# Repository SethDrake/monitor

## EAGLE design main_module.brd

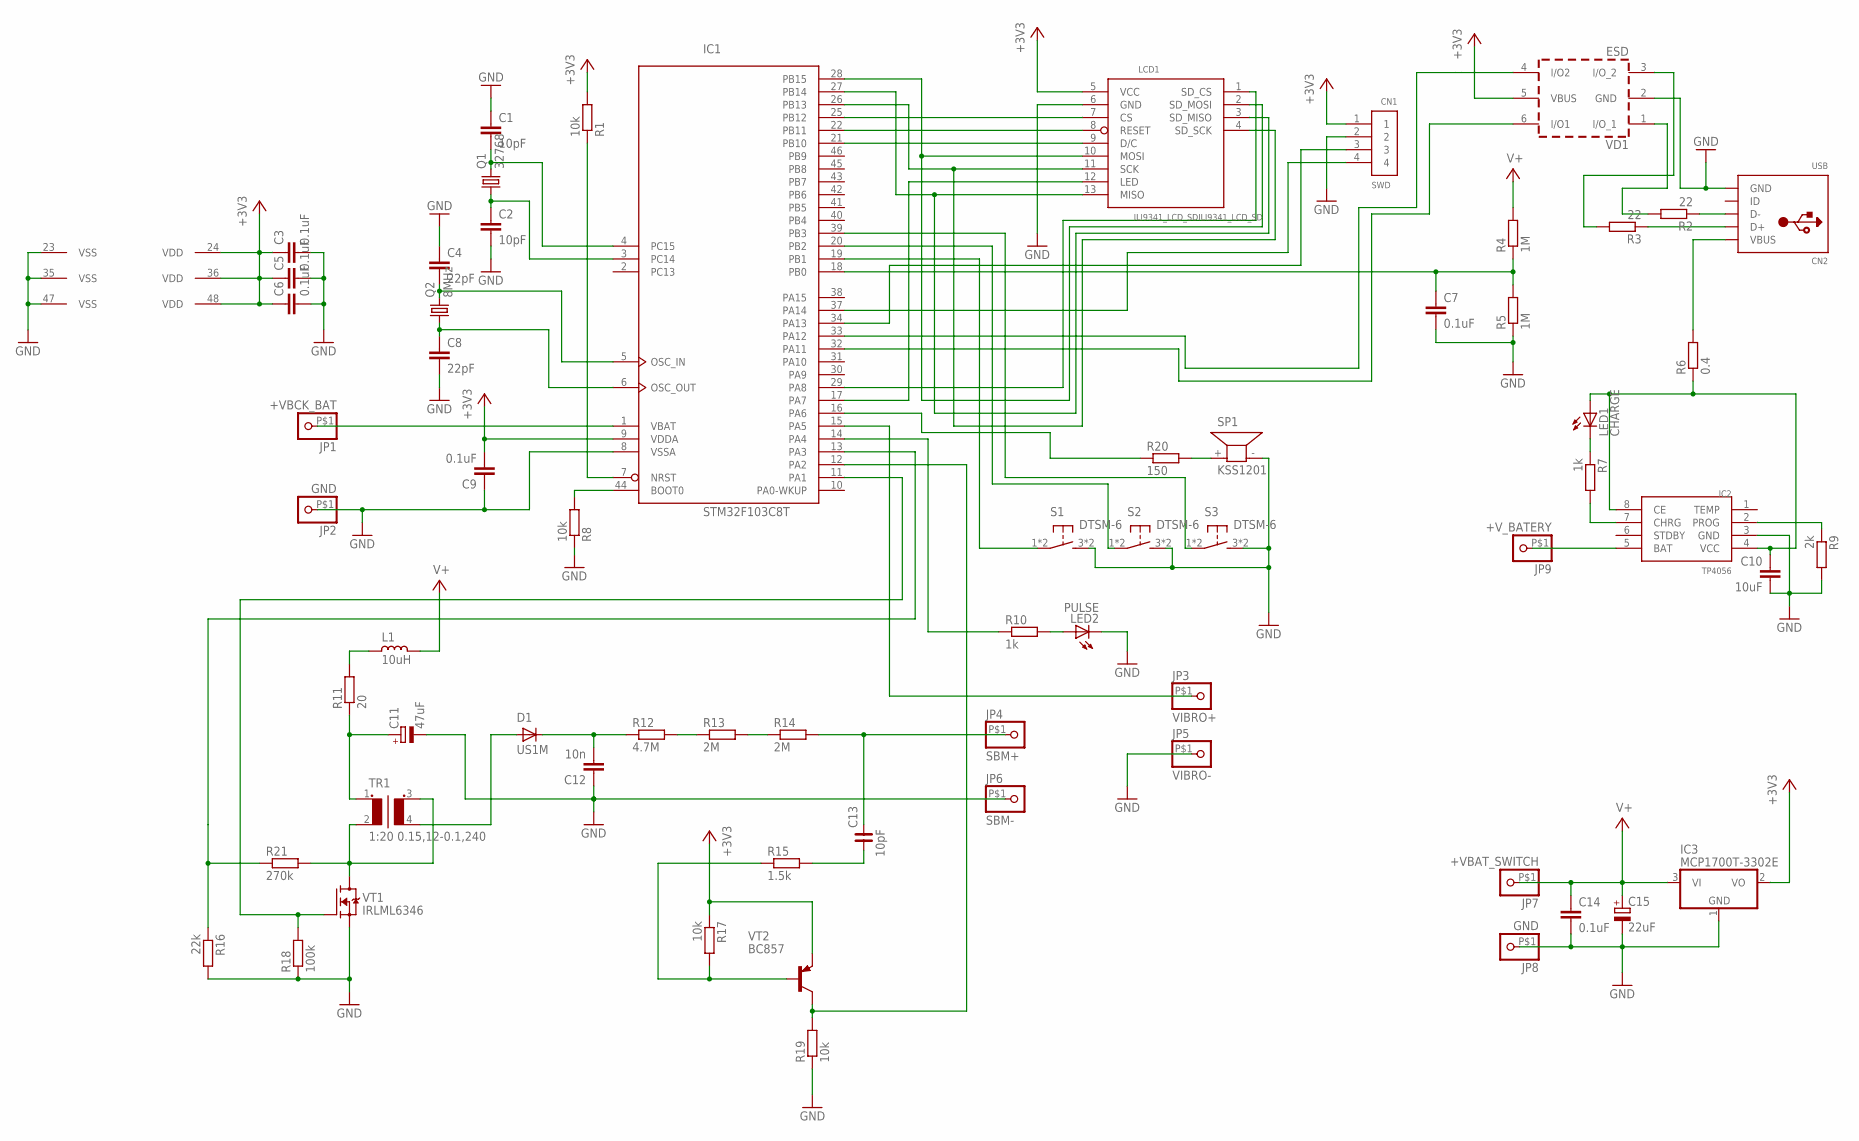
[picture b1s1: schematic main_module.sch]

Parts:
C1, C2: 10pF; C0805
C3, C5, C6, C7, C9, C14: 0.1uF; C0805
C4, C8: 22pF; C0805
C10: 10uF; C0805
C11: 47uF; C/6032-28R
C12: 10n; C1206
C13: 10pF; C1206
C15: 22uF; C/6032-28R
CN1: SWD; 1X04-BIG
CN2: USB; USB-MINIB
D1: US1M; SMA-DO214AC
IC1: STM32F103C8T; LQFP48
IC2: TP4056; SOP-8
IC3: MCP1700T-3302E; SOT23
JP1: +VBCK_BAT; 1X1-BIGPOGO
JP2, JP8: GND; 1X1-BIGPOGO
JP3: VIBRO+; 1X1-BIGPOGO
JP4: SBM+; 1X1-BIGPOGO
JP5: VIBRO-; 1X1-BIGPOGO
JP6: SBM-; 1X1-BIGPOGO
JP7: +VBAT_SWITCH; 1X1-BIGPOGO
JP9: +V_BATERY; 1X1-BIGPOGO
L1: 10uH; L0805
LCD1: ILI9341_LCD_SDILI9341_LCD_SD; ILI9341_LCD_SD
LED1: CHARGE; CHIP-LED0805
LED2: PULSE; LED3MM
Q1: 32768; HC49/S
Q2: 8MHz; HC49/S
R1, R8, R17, R19: 10k; M0805
R2, R3: 22; M0805
R4, R5: 1M; M0805
R6: 0.4; M1206
R7, R10: 1k; M0805
R9: 2k; M0805
R11: 20; M0805
R12: 4.7M; M0805
R13, R14: 2M; M0805
R15: 1.5k; M0805
R16: 22k; M0805
R18: 100k; M0805
R20: 150; M0805
R21: 270k; M0805
S1, S2, S3: DTSM-6
SP1: KSS1201
TR1: 1:20 0.15,12-0.1,240; RING-TRANS
VD1: ESD; SOT-23-6L
VT1: IRLML6346; SOT23
VT2: BC857; SOT23-BCE

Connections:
32OSC_IN: C1.2, IC1.4 (PC15), Q1.2
32OSC_OUT: C2.1, IC1.3 (PC14), Q1.1
+3V3: C3.1, C5.1, C6.1, C9.2, CN1.1, IC1.9 (VDDA), IC1.24 (VDD), IC1.36 (VDD), IC1.48 (VDD), IC3.2 (VO), LCD1.5 (VCC), R1.2, R17.1, VD1.5 (VBUS), VT2.E
+VBCK_BAT: IC1.1 (VBAT), JP1.P$1
+V_BATTERY: IC2.5 (BAT), JP9.P$1
BATT_CTRL: C7.1, IC1.18 (PB0), R4.1, R5.2
GND: C1.1, C2.2, C3.2, C4.1, C5.2, C6.2, C7.2, C8.2, C9.1, C10.2, C11.-, C12.1, C14.2, C15.-, CN1.2, CN2.GND, IC1.8 (VSSA), IC1.23 (VSS), IC1.35 (VSS), IC1.47 (VSS), IC2.3 (GND), IC3.1 (GND), JP2.P$1, JP5.P$1, JP6.P$1, JP8.P$1, LCD1.6 (GND), LED2.K (C), R5.1, R8.1, R9.2, R16.2, R18.1, R19.1, S1.3, S1.4 (3), S2.3, S2.4 (3), S3.3, S3.4 (3), SP1.- (2), VD1.2 (GND), VT1.2 (S)
HV_OUT: C12.2, D1.K (C), R12.1
HV_PULSE: IC1.12 (PA2), R19.2, VT2.C
HV_PUMP: IC1.11 (PA1), R18.2, VT1.1 (G)
HV_TEST: IC1.13 (PA3), R16.1, R21.1
HV_TR_OUT: D1.A, TR1.4 (S2)
KEY1: IC1.19 (PB1), S1.1, S1.2 (1)
KEY2: IC1.20 (PB2), S2.1, S2.2 (1)
KEY3: IC1.39 (PB3), S3.1, S3.2 (1)
LCD_BACKLIGHT: IC1.17 (PA7), LCD1.12 (LED)
LCD_CS: IC1.25 (PB12), LCD1.7 (CS)
LCD_RESET: IC1.22 (PB11), LCD1.8 (RESET)
LCD_RS: IC1.21 (PB10), LCD1.9 (D/C)
LED_PULSE: IC1.14 (PA4), R10.1
MISO: IC1.27 (PB14), LCD1.3 (SD_MISO), LCD1.13 (MISO)
MOSI: IC1.28 (PB15), LCD1.2 (SD_MOSI), LCD1.10 (MOSI)
unnamed: R13.2, R14.1
unnamed: R20.2, SP1.+ (1)
unnamed: R12.2, R13.1
unnamed: IC1.7 (NRST), R1.1
unnamed: L1.2, R11.2
unnamed: C13.1, R15.2
unnamed: C10.1, IC2.4 (VCC), IC2.8 (CE), LED1.A, R6.1
unnamed: LED2.A, R10.2
unnamed: R15.1, R17.2, VT2.B
unnamed: C11.+, R11.1, TR1.1
unnamed: IC1.44 (BOOT0), R8.2
unnamed: CN2.D-, R2.1
unnamed: CN2.D+, R3.1
unnamed: IC2.2 (PROG), R9.1
unnamed: R21.2, TR1.2, TR1.3 (S1), VT1.3 (D)
unnamed: IC2.7 (CHRG), R7.2
unnamed: LED1.C, R7.1
OSC_IN: C4.2, IC1.5 (OSC_IN), Q2.2
OSC_OUT: C8.1, IC1.6 (OSC_OUT), Q2.1
SBM+: C13.2, JP4.P$1, R14.2
SCK: IC1.26 (PB13), LCD1.4 (SD_SCK), LCD1.11 (SCK)
SD_CS: IC1.29 (PA8), LCD1.1 (SD_CS)
SOUND: IC1.16 (PA6), R20.1
SWCLK: CN1.4, IC1.37 (PA14)
SWDIO: CN1.3, IC1.34 (PA13)
USB_DM: IC1.32 (PA11), VD1.6 (I/O1)
USB_DM_PROT: R2.2, VD1.1 (I/O_1)
USB_DP: IC1.33 (PA12), VD1.4 (I/O2)
USB_DP_PROT: R3.2, VD1.3 (I/O_2)
USB_POWER: CN2.VBUS, R6.2
V+: C14.1, C15.+, IC3.3 (VI), JP7.P$1, L1.1, R4.2
VIBRO: IC1.15 (PA5), JP3.P$1

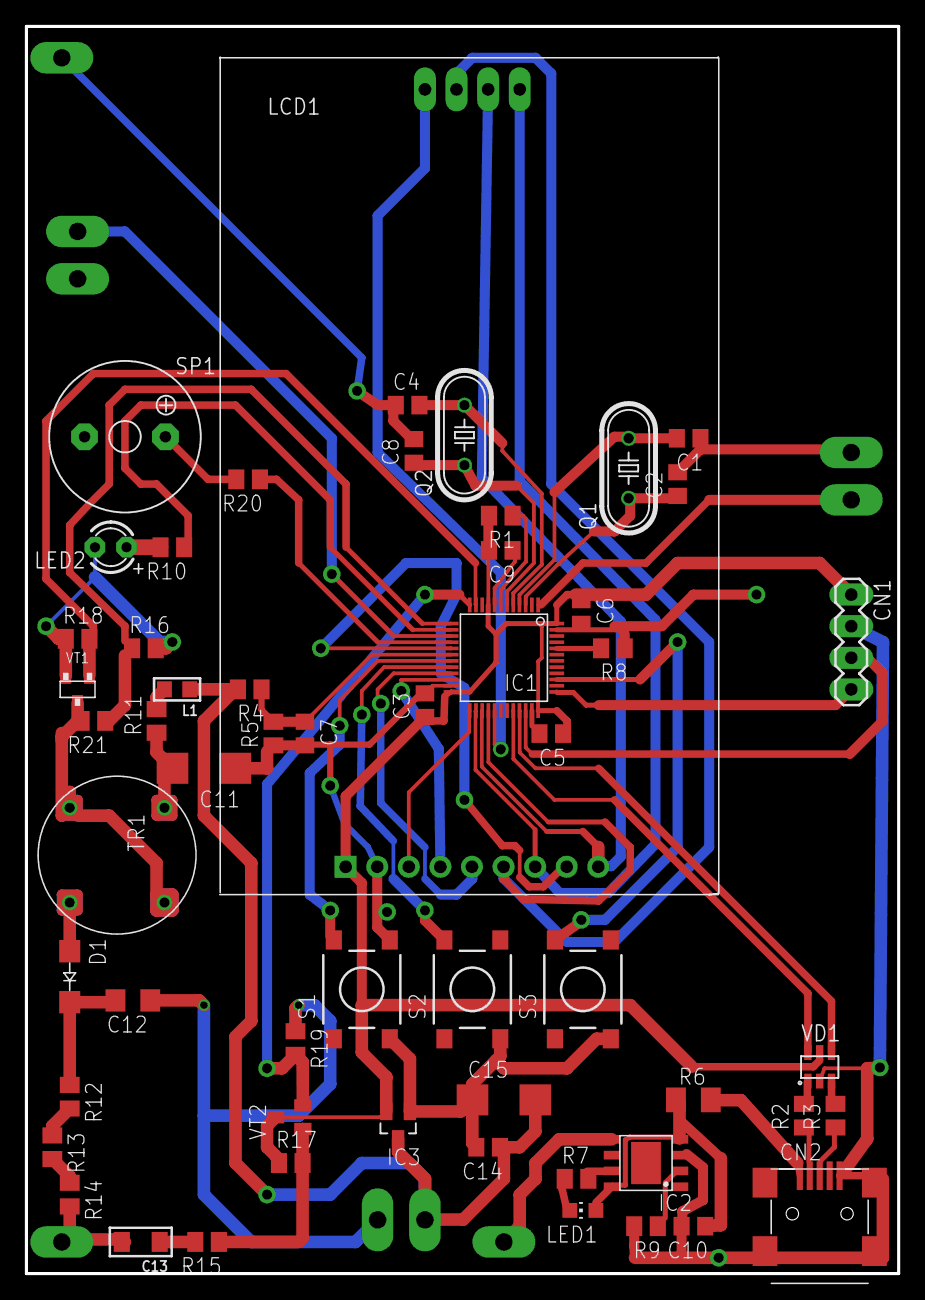
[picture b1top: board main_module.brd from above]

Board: 2 copper layers, 70.2 x 100.3 mm, 65 parts (0 on the bottom side), 54 nets.

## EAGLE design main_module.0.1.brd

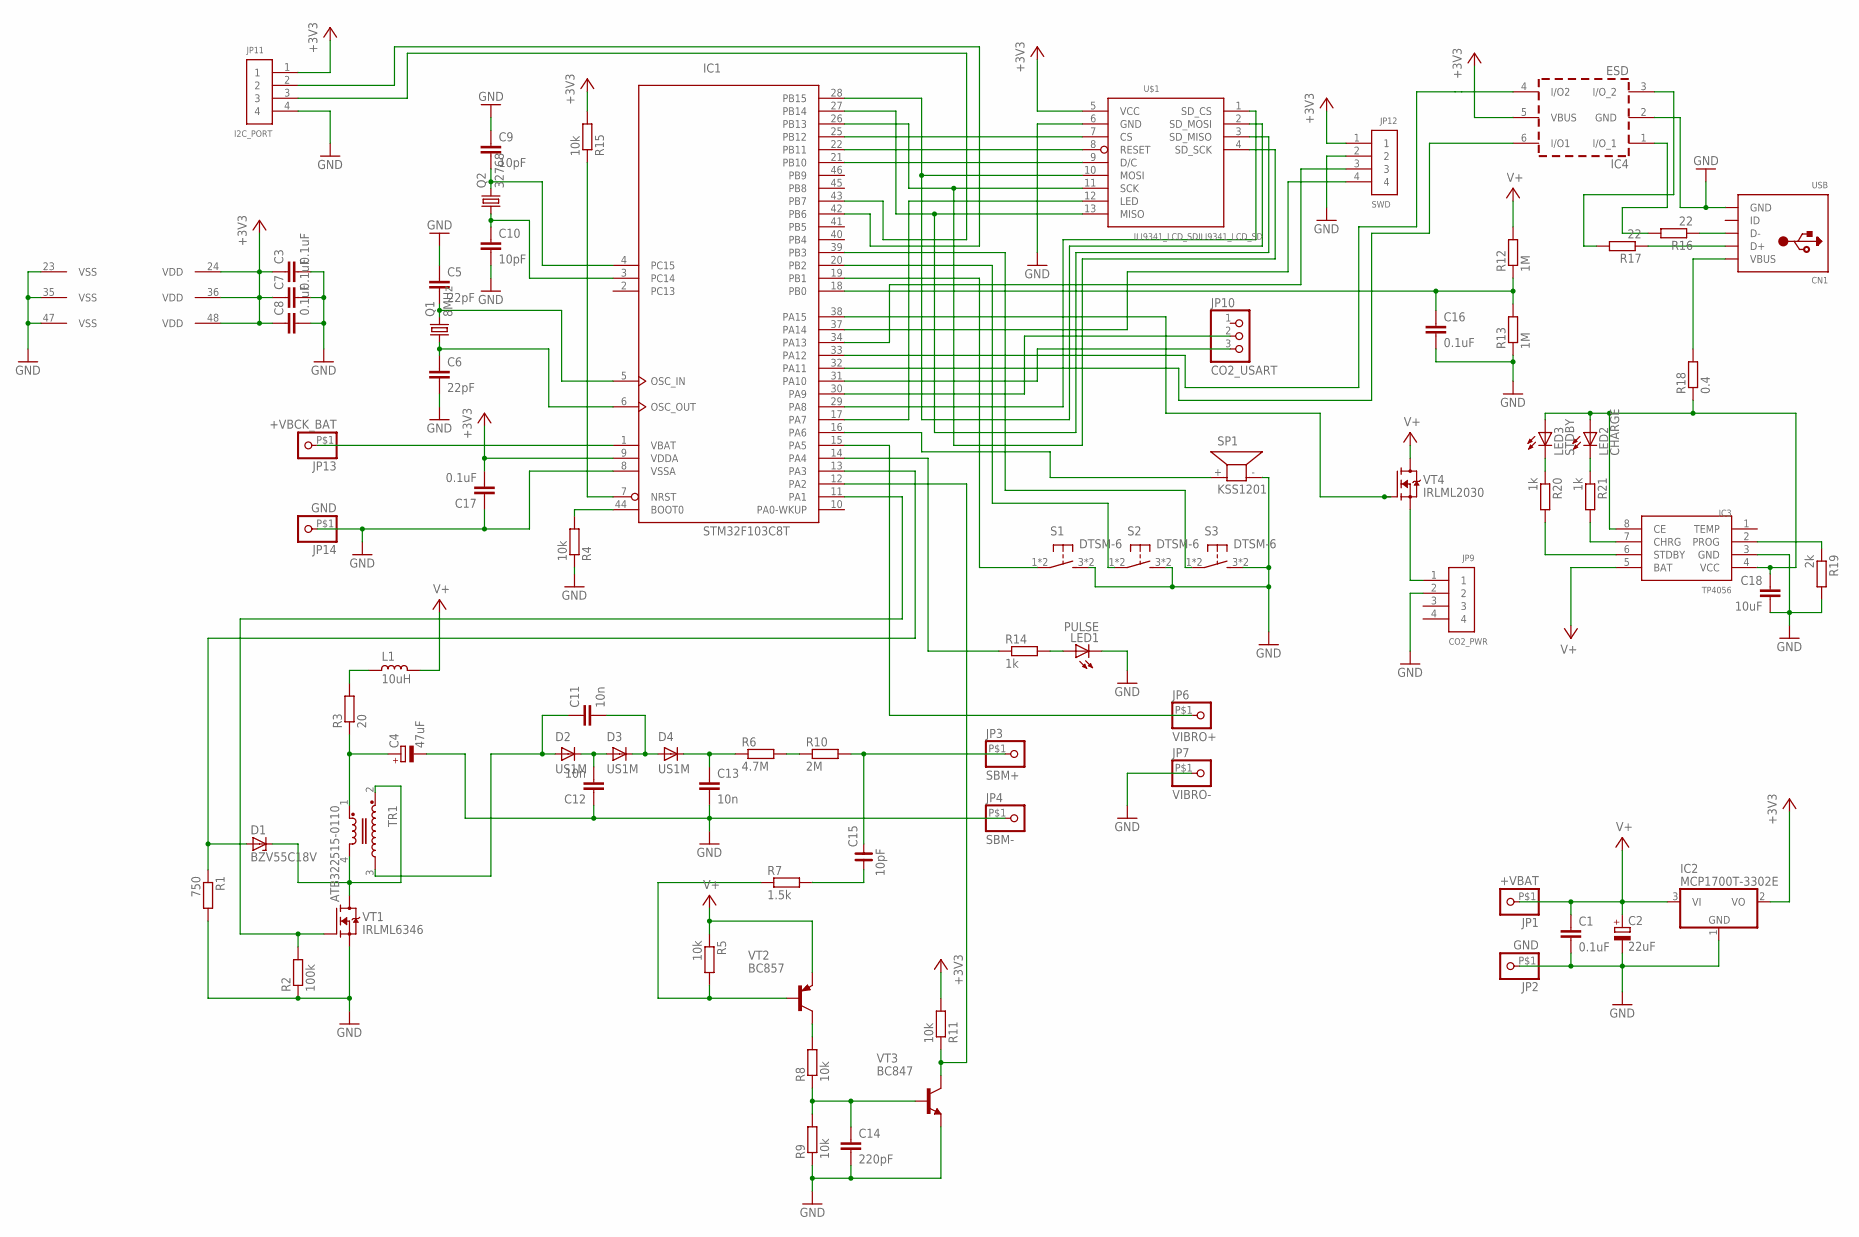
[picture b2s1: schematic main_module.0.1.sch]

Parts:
C1, C3, C7, C8, C16, C17: 0.1uF; C0805
C2: 22uF; C/6032-28R
C4: 47uF; C/6032-28R
C5, C6: 22pF; C0805
C9, C10: 10pF; C0805
C11, C12, C13: 10n; C1206
C14: 220pF; C0805
C15: 10pF; C1206
C18: 10uF; C0805
CN1: USB; USB-MINIB
D1: BZV55C18V; SOD80C
D2, D3, D4: US1M; SMA-DO214AC
IC1: STM32F103C8T; LQFP48
IC2: MCP1700T-3302E; SOT23
IC3: TP4056; SOP-8
IC4: ESD; SOT-23-6L
JP1: +VBAT; 1X1-BIGPOGO
JP2, JP14: GND; 1X1-BIGPOGO
JP3: SBM+; 1X1-BIGPOGO
JP4: SBM-; 1X1-BIGPOGO
JP6: VIBRO+; 1X1-BIGPOGO
JP7: VIBRO-; 1X1-BIGPOGO
JP9: CO2_PWR; 1X04-BIG
JP10: CO2_USART; 1X03
JP11: I2C_PORT; 1X04-BIG
JP12: SWD; 1X04-BIG
JP13: +VBCK_BAT; 1X1-BIGPOGO
L1: 10uH; L0805
LED1: PULSE; LED3MM
LED2: CHARGE; CHIP-LED0805
LED3: STDBY; CHIP-LED0805
Q1: 8MHz; HC49/S
Q2: 32768; HC49/S
R1: 750; M0805
R2: 100k; M0805
R3: 20; M0805
R4, R5, R8, R9, R11, R15: 10k; M0805
R6: 4.7M; M0805
R7: 1.5k; M0805
R10: 2M; M0805
R12, R13: 1M; M0805
R14, R20, R21: 1k; M0805
R16, R17: 22; M0805
R18: 0.4; M1206
R19: 2k; M0805
S1, S2, S3: DTSM-6
SP1: KSS1201
TR1: ATB322515-0110; ATB3225
U$1: ILI9341_LCD_SDILI9341_LCD_SD; ILI9341_LCD_SD
VT1: IRLML6346; SOT23
VT2: BC857; SOT23-BCE
VT3: BC847; SOT23
VT4: IRLML2030; SOT23

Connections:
32OSC_IN: C9.2, IC1.4 (PC15), Q2.2
32OSC_OUT: C10.1, IC1.3 (PC14), Q2.1
+3V3: C3.1, C7.1, C8.1, C17.2, IC1.9 (VDDA), IC1.24 (VDD), IC1.36 (VDD), IC1.48 (VDD), IC2.2 (VO), IC4.5 (VBUS), JP11.1, JP12.1, R11.2, R15.2, U$1.5 (VCC)
+VBCK_BAT: IC1.1 (VBAT), JP13.P$1
BATT_CTRL: C16.1, IC1.18 (PB0), R12.1, R13.2
CO2_PWR_CONTROL: IC1.38 (PA15), VT4.1 (G)
GND: C1.2, C2.-, C3.2, C4.-, C5.1, C6.2, C7.2, C8.2, C9.1, C10.2, C12.1, C13.2, C14.2, C16.2, C17.1, C18.2, CN1.GND, IC1.8 (VSSA), IC1.23 (VSS), IC1.35 (VSS), IC1.47 (VSS), IC2.1 (GND), IC3.3 (GND), IC4.2 (GND), JP2.P$1, JP4.P$1, JP7.P$1, JP9.2, JP11.4, JP12.2, JP14.P$1, LED1.K (C), R1.2, R2.1, R4.1, R9.1, R13.1, R19.2, S1.3, S1.4 (3), S2.3, S2.4 (3), S3.3, S3.4 (3), SP1.- (2), U$1.6 (GND), VT1.2 (S), VT3.2 (E)
HV_MUL_IN: C11.1, D2.A, TR1.3
HV_PULSE: IC1.12 (PA2), R11.1, VT3.3 (C)
HV_PUMP: IC1.11 (PA1), R2.2, VT1.1 (G)
HV_TEST: D1.A, IC1.13 (PA3), R1.1
I2C_SCL: IC1.42 (PB6), JP11.2
I2C_SDA: IC1.43 (PB7), JP11.3
KEY1: IC1.19 (PB1), S1.1, S1.2 (1)
KEY2: IC1.20 (PB2), S2.1, S2.2 (1)
KEY3: IC1.39 (PB3), S3.1, S3.2 (1)
LCD_BACKLIGHT: IC1.17 (PA7), U$1.12 (LED)
LCD_CS: IC1.25 (PB12), U$1.7 (CS)
LCD_RESET: IC1.22 (PB11), U$1.8 (RESET)
LCD_RS: IC1.21 (PB10), U$1.9 (D/C)
LED_PULSE: IC1.14 (PA4), R14.1
MISO: IC1.27 (PB14), U$1.3 (SD_MISO), U$1.13 (MISO)
MOSI: IC1.28 (PB15), U$1.2 (SD_MOSI), U$1.10 (MOSI)
unnamed: JP9.1, VT4.2 (S)
unnamed: C12.2, D2.K (C), D3.A
unnamed: C11.2, D3.K (C), D4.A
unnamed: C13.1, D4.K (C), R6.1
unnamed: R6.2, R10.1
unnamed: IC1.7 (NRST), R15.1
unnamed: L1.2, R3.2
unnamed: C15.1, R7.2
unnamed: C18.1, IC3.4 (VCC), IC3.8 (CE), LED2.A, LED3.A, R18.1
unnamed: LED1.A, R14.2
unnamed: R5.2, R7.1, VT2.B
unnamed: R8.2, VT2.C
unnamed: C14.1, R8.1, R9.2, VT3.1 (B)
unnamed: C4.+, R3.1, TR1.1
unnamed: IC1.44 (BOOT0), R4.2
unnamed: CN1.D-, R16.1
unnamed: CN1.D+, R17.1
unnamed: IC3.2 (PROG), R19.1
unnamed: D1.C, TR1.2, TR1.4, VT1.3 (D)
unnamed: IC3.7 (CHRG), R21.2
unnamed: LED2.C, R21.1
unnamed: LED3.C, R20.1
unnamed: IC3.6 (STDBY), R20.2
OSC_IN: C5.2, IC1.5 (OSC_IN), Q1.2
OSC_OUT: C6.1, IC1.6 (OSC_OUT), Q1.1
SBM+: C15.2, JP3.P$1, R10.2
SCK: IC1.26 (PB13), U$1.4 (SD_SCK), U$1.11 (SCK)
SD_CS: IC1.29 (PA8), U$1.1 (SD_CS)
SOUND: IC1.16 (PA6), SP1.+ (1)
SWCLK: IC1.37 (PA14), JP12.4
SWDIO: IC1.34 (PA13), JP12.3
USART_RX: IC1.31 (PA10), JP10.3
USART_TX: IC1.30 (PA9), JP10.2
USB_DM: IC1.32 (PA11), IC4.6 (I/O1)
USB_DM_PROT: IC4.1 (I/O_1), R16.2
USB_DP: IC1.33 (PA12), IC4.4 (I/O2)
USB_DP_PROT: IC4.3 (I/O_2), R17.2
USB_POWER: CN1.VBUS, R18.2
V+: C1.1, C2.+, IC2.3 (VI), IC3.5 (BAT), JP1.P$1, L1.1, R5.1, R12.2, VT2.E, VT4.3 (D)
VIBRO: IC1.15 (PA5), JP6.P$1

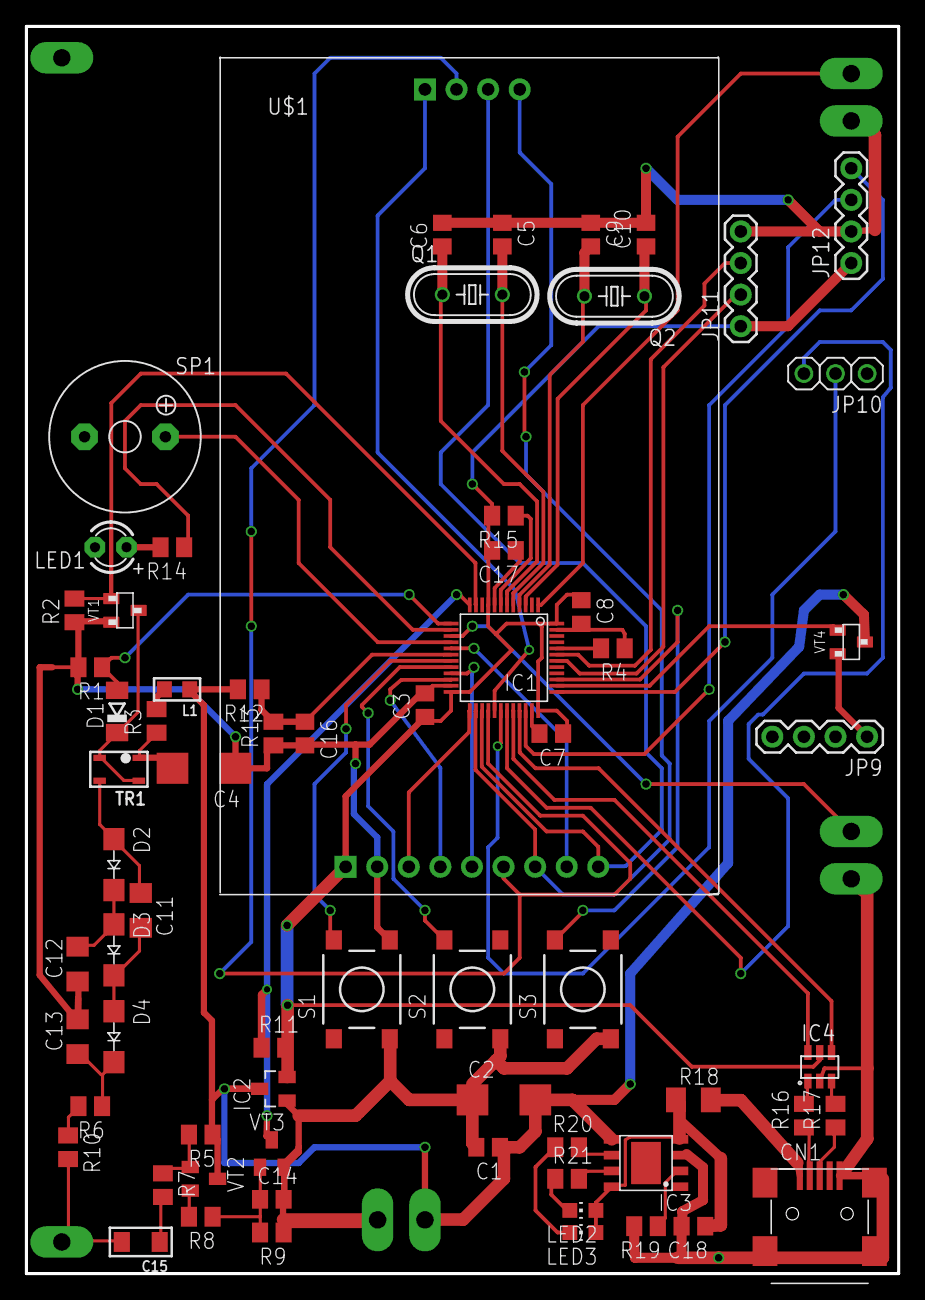
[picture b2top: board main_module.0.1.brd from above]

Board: 2 copper layers, 70.2 x 100.3 mm, 76 parts (0 on the bottom side), 63 nets.

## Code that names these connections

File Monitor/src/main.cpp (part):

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	GPIO_Init(SPI_PORT, &GPIO_InitStructure);
	
	   /* Configure HV pins */
	GPIO_InitStructure.GPIO_Pin = HV_PUMP_PIN;
	GPIO_InitStructure.GPIO_Mode = GPIO_Mode_AF_PP;
	GPIO_InitStructure.GPIO_Speed = GPIO_Speed_10MHz;
	GPIO_Init(HV_PUMP_PORT, &GPIO_InitStructure);
	GPIO_InitStructure.GPIO_Pin = HV_PULSE_PIN | HV_TEST_PIN;
	GPIO_InitStructure.GPIO_Mode = GPIO_Mode_IN_FLOATING;
	GPIO_InitStructure.GPIO_Speed = GPIO_Speed_50MHz;
	GPIO_Init(HV_PUMP_PORT, &GPIO_InitStructure);
	   /* Configure INDICATION pins */
	GPIO_InitStructure.GPIO_Pin = IND_PULSE_PIN | IND_VIBRATE_PIN;
	GPIO_InitStructure.GPIO_Mode = GPIO_Mode_Out_PP;
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	GPIO_InitStructure.GPIO_Pin = BATT_CTL_V_PIN;
	GPIO_InitStructure.GPIO_Mode = GPIO_Mode_AIN;
	GPIO_InitStructure.GPIO_Speed = GPIO_Speed_2MHz;
	GPIO_Init(BATT_CTRL_PORT, &GPIO_InitStructure);
	
	/* Configure KEYBOARD pins */
	GPIO_InitStructure.GPIO_Pin = KEY_1_PIN | KEY_2_PIN | KEY_3_PIN;
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	ADC_Cmd(ADC1, DISABLE);
	//switch pins to AIN mode
	GPIO_InitTypeDef  GPIO_InitStructure;
	GPIO_InitStructure.GPIO_Pin = GPIO_Pin_All & !(HV_PULSE_PIN); //disable port A excluding impulse input
	GPIO_InitStructure.GPIO_Mode = GPIO_Mode_AIN;
	GPIO_Init(GPIOA, &GPIO_InitStructure);
	GPIO_InitStructure.GPIO_Pin = GPIO_Pin_All & !(ILI9341_PIN_RESET); //disable port B excl display pins
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
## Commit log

2017-09-23 power scheme improvement
2017-12-04 improvements
2018-10-23 small improvements, release build
2019-09-02 project structure fixes
2019-09-02 project fixes added docs
2019-09-03 small improvements (save last state)
2019-09-04 added IWDG
2019-09-06 low battery shutdown and watchdog improvements
2019-09-06 watchdog improvements
2019-09-06 adjust low battery shutdown threshold
2019-09-20 fix batt adc coeff
2019-10-09 fix Vbat measurement
2019-10-09 vgdb settings

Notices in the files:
parts and their libraries:
rc-master-smd: Copyright (C) 2007, Bob Starr
atb3225-tdk: Copyright (C) 2008, Bob Starr
